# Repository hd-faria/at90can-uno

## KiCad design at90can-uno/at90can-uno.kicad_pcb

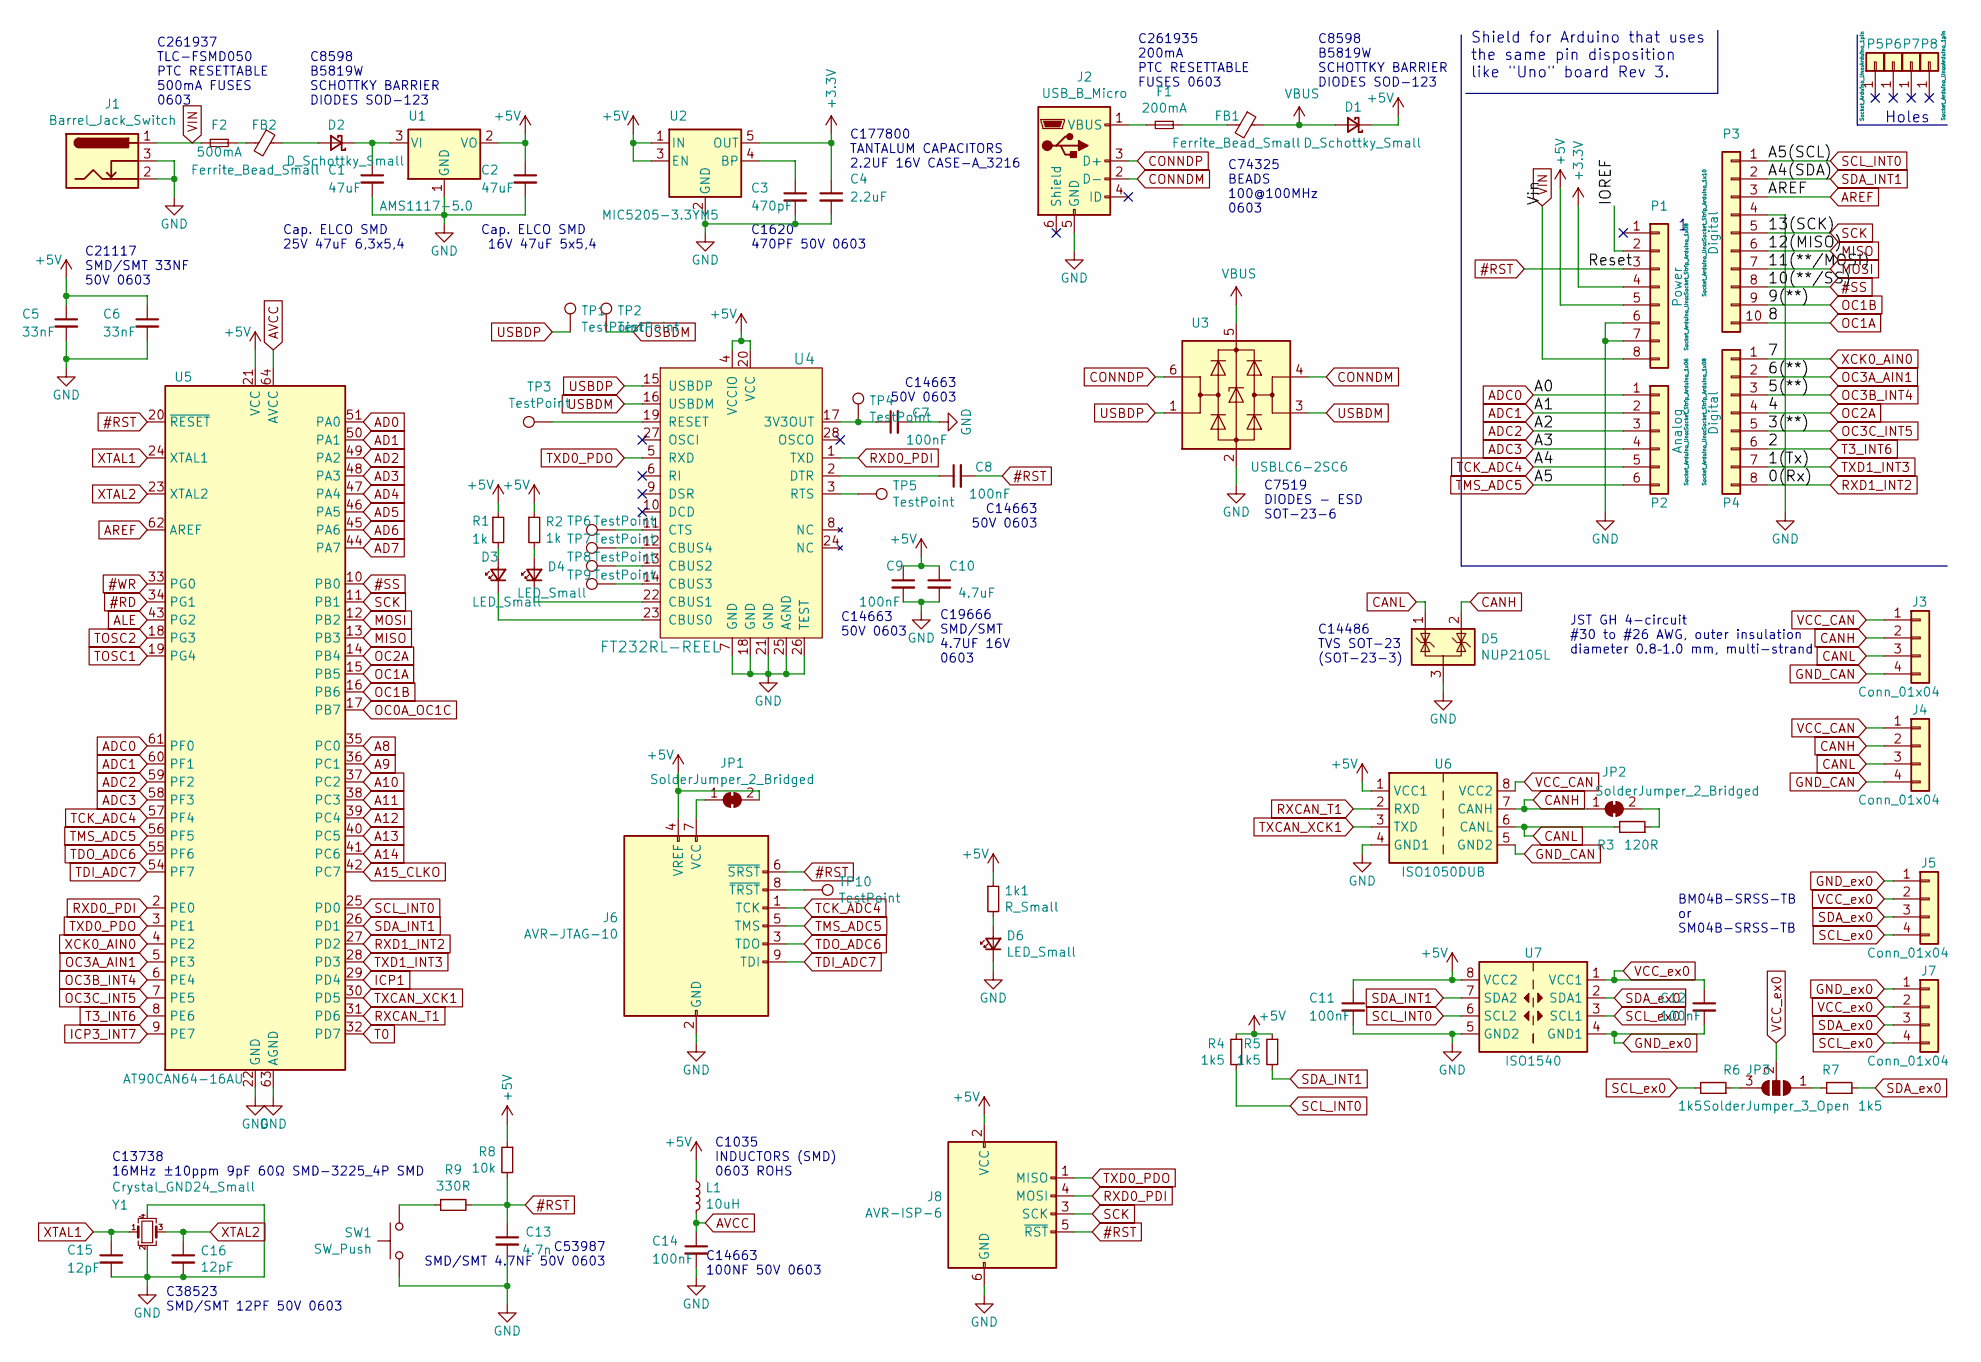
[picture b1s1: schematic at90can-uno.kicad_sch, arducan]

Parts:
1k1: R_Small; R_0603_1608Metric_Pad1.05x0.95mm_HandSolder
C1: 47uF; CP_Elec_6.3x5.4
C2: 47uF; CP_Elec_5x5.4
C3: 470pF; C_0603_1608Metric_Pad1.05x0.95mm_HandSolder
C4: 2.2uF; CP_EIA-3216-18_Kemet-A
C5, C6: 33nF; C_0603_1608Metric_Pad1.05x0.95mm_HandSolder
C7, C8, C9, C11, C12, C14: 100nF; C_0603_1608Metric_Pad1.05x0.95mm_HandSolder
C10: 4.7uF; C_0603_1608Metric_Pad1.05x0.95mm_HandSolder
C13: 4.7n; C_0603_1608Metric_Pad1.05x0.95mm_HandSolder
C15, C16: 12pF; C_0603_1608Metric_Pad1.05x0.95mm_HandSolder
D1, D2: D_Schottky_Small; D_SOD-123
D3, D4, D6: LED_Small; LED_0603_1608Metric_Pad1.05x0.95mm_HandSolder
D5: NUP2105L; SOT-23
F1: 200mA; Fuse_0603_1608Metric_Pad1.05x0.95mm_HandSolder
F2: 500mA; Fuse_0603_1608Metric_Pad1.05x0.95mm_HandSolder
FB1, FB2: Ferrite_Bead_Small; L_0603_1608Metric_Pad1.05x0.95mm_HandSolder
J1: Barrel_Jack_Switch; BarrelJack_CUI_PJ-063AH_Horizontal
J2: USB_B_Micro; USB_Micro-B_Amphenol_10103594-0001LF_Horizontal
J3, J4: Conn_01x04; JST_GH_BM04B-GHS-TBT_1x04-1MP_P1.25mm_Vertical
J5, J7: Conn_01x04; JST_SH_BM04B-SRSS-TB_1x04-1MP_P1.00mm_Vertical
J6: AVR-JTAG-10; IDC-Header_2x05_P2.54mm_Vertical
J8: AVR-ISP-6; IDC-Header_2x03_P2.54mm_Vertical
JP1, JP2: SolderJumper_2_Bridged; SolderJumper-2_P1.3mm_Bridged_Pad1.0x1.5mm
JP3: SolderJumper_3_Open; SolderJumper-3_P1.3mm_Open_Pad1.0x1.5mm_NumberLabels
L1: 10uH; L_0603_1608Metric_Pad1.05x0.95mm_HandSolder
P1: Power; Socket_Strip_Arduino_1x08
P2: Analog; Socket_Strip_Arduino_1x06
P3: Digital; Socket_Strip_Arduino_1x10
P4: Digital; Socket_Strip_Arduino_1x08
P5, P6, P7, P8: CONN_01X01; Arduino_1pin
R1, R2: 1k; R_0603_1608Metric_Pad1.05x0.95mm_HandSolder
R3: 120R; R_0603_1608Metric_Pad1.05x0.95mm_HandSolder
R4, R5, R6, R7: 1k5; R_0603_1608Metric_Pad1.05x0.95mm_HandSolder
R8: 10k; R_0603_1608Metric_Pad1.05x0.95mm_HandSolder
R9: 330R; R_0603_1608Metric_Pad1.05x0.95mm_HandSolder
SW1: SW_Push; TACTILE_SWITCH_SMD_6.0X3.5MM
TP1, TP2, TP3, TP4, TP5, TP6, TP7, TP8, TP9, TP10: TestPoint; Pin_D0.7mm_L6.5mm_W1.8mm_FlatFork
U1: AMS1117-5.0; SOT-223-3_TabPin2
U2: MIC5205-3.3YM5; SOT-23-5
U3: USBLC6-2SC6; SOT-23-6
U4: FT232RL-REEL; SSOP-28_W5.30mm; MPN FT232RL-REEL; Digi-Key_PN 768-1007-1-ND
U5: AT90CAN64-16AU; TQFP-64_14x14mm_P0.8mm
U6: ISO1050DUB; SOP-8_6.62x9.15mm_P2.54mm
U7: ISO1540; SOIC-8_3.9x4.9mm_P1.27mm
Y1: Crystal_GND24_Small; Crystal_SMD_3225-4Pin_3.2x2.5mm_HandSoldering

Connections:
#RD: U5.34 (PG1)
#RST: C8.2, C13.1, J6.6 (~SRST), J8.5 (~RST), P1.3, R8.2, R9.2, U5.20 (~RESET)
#SS: P3.8, U5.10 (PB0)
#WR: U5.33 (PG0)
+3V3: C4.1, P1.4, U2.5 (OUT)
+5V: 1k1.1, C2.1, C5.1, C6.1, C9.1, C10.1, C11.1, D1.1 (K), J6.4 (VREF), J8.2 (VCC), JP1.2 (B), L1.1, P1.5, R1.1, R2.1, R4.1, R5.1, R8.1, U1.2 (VO), U2.1 (IN), U2.3 (EN), U4.4 (VCCIO), U4.20 (VCC), U5.21 (VCC), U5.52 (VCC), U6.1 (VCC1), U7.8 (VCC2)
/IOREF: P1.2
A8: U5.35 (PC0)
A9: U5.36 (PC1)
A10: U5.37 (PC2)
A11: U5.38 (PC3)
A12: U5.39 (PC4)
A13: U5.40 (PC5)
A14: U5.41 (PC6)
A15_CLKO: U5.42 (PC7)
AD0: U5.51 (PA0)
AD1: U5.50 (PA1)
AD2: U5.49 (PA2)
AD3: U5.48 (PA3)
AD4: U5.47 (PA4)
AD5: U5.46 (PA5)
AD6: U5.45 (PA6)
AD7: U5.44 (PA7)
ADC0: P2.1, U5.61 (PF0)
ADC1: P2.2, U5.60 (PF1)
ADC2: P2.3, U5.59 (PF2)
ADC3: P2.4, U5.58 (PF3)
ALE: U5.43 (PG2)
AREF: P3.3, U5.62 (AREF)
AVCC: C14.1, L1.2, U5.64 (AVCC)
CANH: D5.2 (K), J3.2, J4.2, JP2.1 (A), U6.7 (CANH)
CANL: D5.1 (K), J3.3, J4.3, R3.2, U6.6 (CANL)
CONNDM: J2.2 (D-), U3.4 (I/O2)
CONNDP: J2.3 (D+), U3.6 (I/O1)
GND: C1.2, C2.2, C3.2, C4.2, C5.2, C6.2, C7.2, C9.2, C10.2, C11.2, C13.2, C14.2, C15.2, C16.2, D5.3 (A), D6.1 (K), J1.2, J1.3, J2.5 (GND), J6.2 (GND), J6.10 (GND), J8.6 (GND), P1.6, P1.7, P3.4, SW1.2, U1.1 (GND), U2.2 (GND), U3.2 (GND), U4.7 (GND), U4.18 (GND), U4.21 (GND), U4.25 (AGND), U4.26 (TEST), U5.22 (GND), U5.53 (GND), U5.63 (AGND), U6.4 (GND1), U7.5 (GND2), Y1.2, Y1.4
GND_CAN: J3.4, J4.4, U6.5 (GND2)
GND_ex0: C12.2, J5.1, J7.1, U7.4 (GND1)
ICP1: U5.29 (PD4)
ICP3_INT7: U5.9 (PE7)
MISO: P3.6, U5.13 (PB3)
MOSI: P3.7, U5.12 (PB2)
unnamed: 1k1.2, D6.2 (A)
unnamed: C1.1, D2.1 (K), U1.3 (VI)
unnamed: C3.1, U2.4 (BP)
unnamed: C7.1, TP4.1, U4.17 (3V3OUT)
unnamed: C8.1, U4.2 (DTR)
unnamed: D2.2 (A), FB2.1
unnamed: D3.1 (K), U4.23 (CBUS0)
unnamed: D3.2 (A), R1.2
unnamed: D4.1 (K), U4.22 (CBUS1)
unnamed: D4.2 (A), R2.2
unnamed: F1.1, J2.1 (VBUS)
unnamed: F1.2, FB1.2
unnamed: F2.2, FB2.2
unnamed: J6.7 (VCC), JP1.1 (A)
unnamed: J6.8 (~TRST), TP10.1
unnamed: JP2.2 (B), R3.1
unnamed: JP3.1 (A), R7.2
unnamed: JP3.3 (B), R6.1
unnamed: R9.1, SW1.1
unnamed: TP3.1, U4.19 (RESET)
unnamed: TP5.1, U4.3 (RTS)
unnamed: TP6.1, U4.11 (CTS)
unnamed: TP7.1, U4.12 (CBUS4)
unnamed: TP8.1, U4.13 (CBUS2)
unnamed: TP9.1, U4.14 (CBUS3)
OC0A_OC1C: U5.17 (PB7)
OC1A: P3.10, U5.15 (PB5)
OC1B: P3.9, U5.16 (PB6)
OC2A: P4.4, U5.14 (PB4)
OC3A_AIN1: P4.2, U5.5 (PE3)
OC3B_INT4: P4.3, U5.6 (PE4)
OC3C_INT5: P4.5, U5.7 (PE5)
RXCAN_T1: U5.31 (PD6), U6.2 (RXD)
RXD0_PDI: J8.4 (MOSI), U4.1 (TXD), U5.2 (PE0)
RXD1_INT2: P4.8, U5.27 (PD2)
SCK: J8.3 (SCK), P3.5, U5.11 (PB1)
SCL_INT0: P3.1, R4.2, U5.25 (PD0), U7.6 (SCL2)
SCL_ex0: J5.4, J7.4, R6.2, U7.3 (SCL1)
SDA_INT1: P3.2, R5.2, U5.26 (PD1), U7.7 (SDA2)
SDA_ex0: J5.3, J7.3, R7.1, U7.2 (SDA1)
T0: U5.32 (PD7)
T3_INT6: P4.6, U5.8 (PE6)
TCK_ADC4: J6.1 (TCK), P2.5, U5.57 (PF4)
TDI_ADC7: J6.9 (TDI), U5.54 (PF7)
TDO_ADC6: J6.3 (TDO), U5.55 (PF6)
TMS_ADC5: J6.5 (TMS), P2.6, U5.56 (PF5)
TOSC1: U5.19 (PG4)
TOSC2: U5.18 (PG3)
TXCAN_XCK1: U5.30 (PD5), U6.3 (TXD)
TXD0_PDO: J8.1 (MISO), U4.5 (RXD), U5.3 (PE1)
TXD1_INT3: P4.7, U5.28 (PD3)
USBDM: TP2.1, U3.3 (I/O2), U4.16 (USBDM)
USBDP: TP1.1, U3.1 (I/O1), U4.15 (USBDP)
VBUS: D1.2 (A), FB1.1, U3.5 (VBUS)
VCC_CAN: J3.1, J4.1, U6.8 (VCC2)
VCC_ex0: C12.1, J5.2, J7.2, JP3.2 (C), U7.1 (VCC1)
VIN: F2.1, J1.1, P1.8
XCK0_AIN0: P4.1, U5.4 (PE2)
XTAL1: C15.1, U5.24 (XTAL1), Y1.1
XTAL2: C16.1, U5.23 (XTAL2), Y1.3

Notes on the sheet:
C13738 16MHz ±10ppm 9pF 60Ω SMD-3225_4P SMD
C74325 BEADS 100@100MHz 0603
C14663 50V 0603
C38523 SMD/SMT 12PF 50V 0603
C8598 B5819W SCHOTTKY BARRIER DIODES SOD-123
Shield for Arduino that uses the same pin disposition like "Uno" board Rev 3.
C7519 DIODES - ESD SOT-23-6
BM04B-SRSS-TB or SM04B-SRSS-TB
C21117 SMD/SMT 33NF 50V 0603
C14486 TVS SOT-23 (SOT-23-3)
C19666 SMD/SMT 4.7UF 16V 0603
Holes
Cap. ELCO SMD 25V 47uF 6,3x5,4
C1035 INDUCTORS (SMD) 0603 ROHS
C1620 470PF 50V 0603
C261937 TLC-FSMD050 PTC RESETTABLE 500mA FUSES 0603
Cap. ELCO SMD 16V 47uF 5x5,4
C14663 100NF 50V 0603
C261935 200mA PTC RESETTABLE FUSES 0603
JST GH 4-circuit #30 to #26 AWG, outer insulation diameter 0.8–1.0 mm, multi-strand
C53987 SMD/SMT 4.7NF 50V 0603
C177800 TANTALUM CAPACITORS 2.2UF 16V CASE-A_3216

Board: 4 copper layers, 75 parts (7 on the bottom side), 75 nets, no tracks yet.

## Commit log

2020-08-15 first commit of the circuit
2020-08-15 add gitignore
2020-08-15 update gitignores
2020-08-15 update schematic
2022-03-02 update to new kicad
